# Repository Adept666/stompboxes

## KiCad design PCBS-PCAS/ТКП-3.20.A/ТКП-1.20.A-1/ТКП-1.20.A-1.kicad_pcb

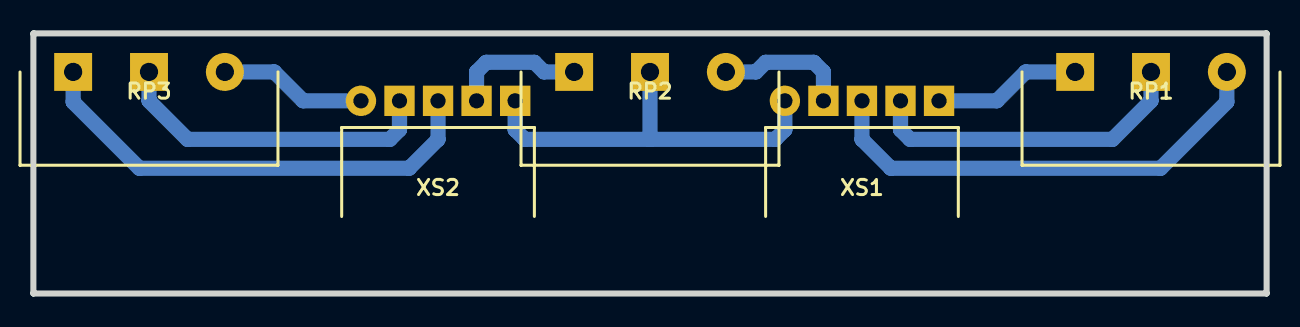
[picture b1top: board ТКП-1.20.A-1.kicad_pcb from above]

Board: 2 copper layers, 81.3 x 17.1 mm, 5 parts (0 on the bottom side), 9 nets.

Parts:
RP1: RP1: B100K; RP-PDB181-K-20-P
RP2: RP2: B5K; RP-PDB181-K-20-P
RP3: RP3: A500K; RP-PDB181-K-20-P
XS1, XS2: PBS-05R; CON-PBS-05R

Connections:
unnamed: RP1.1, XS1.3
unnamed: RP1.2, XS1.4
unnamed: RP1.3, XS1.5
unnamed: RP2.1, XS1.2
unnamed: RP2.2, XS1.1, XS2.5
unnamed: RP2.3, XS2.4
unnamed: RP3.1, XS2.1
unnamed: RP3.2, XS2.2
unnamed: RP3.3, XS2.3

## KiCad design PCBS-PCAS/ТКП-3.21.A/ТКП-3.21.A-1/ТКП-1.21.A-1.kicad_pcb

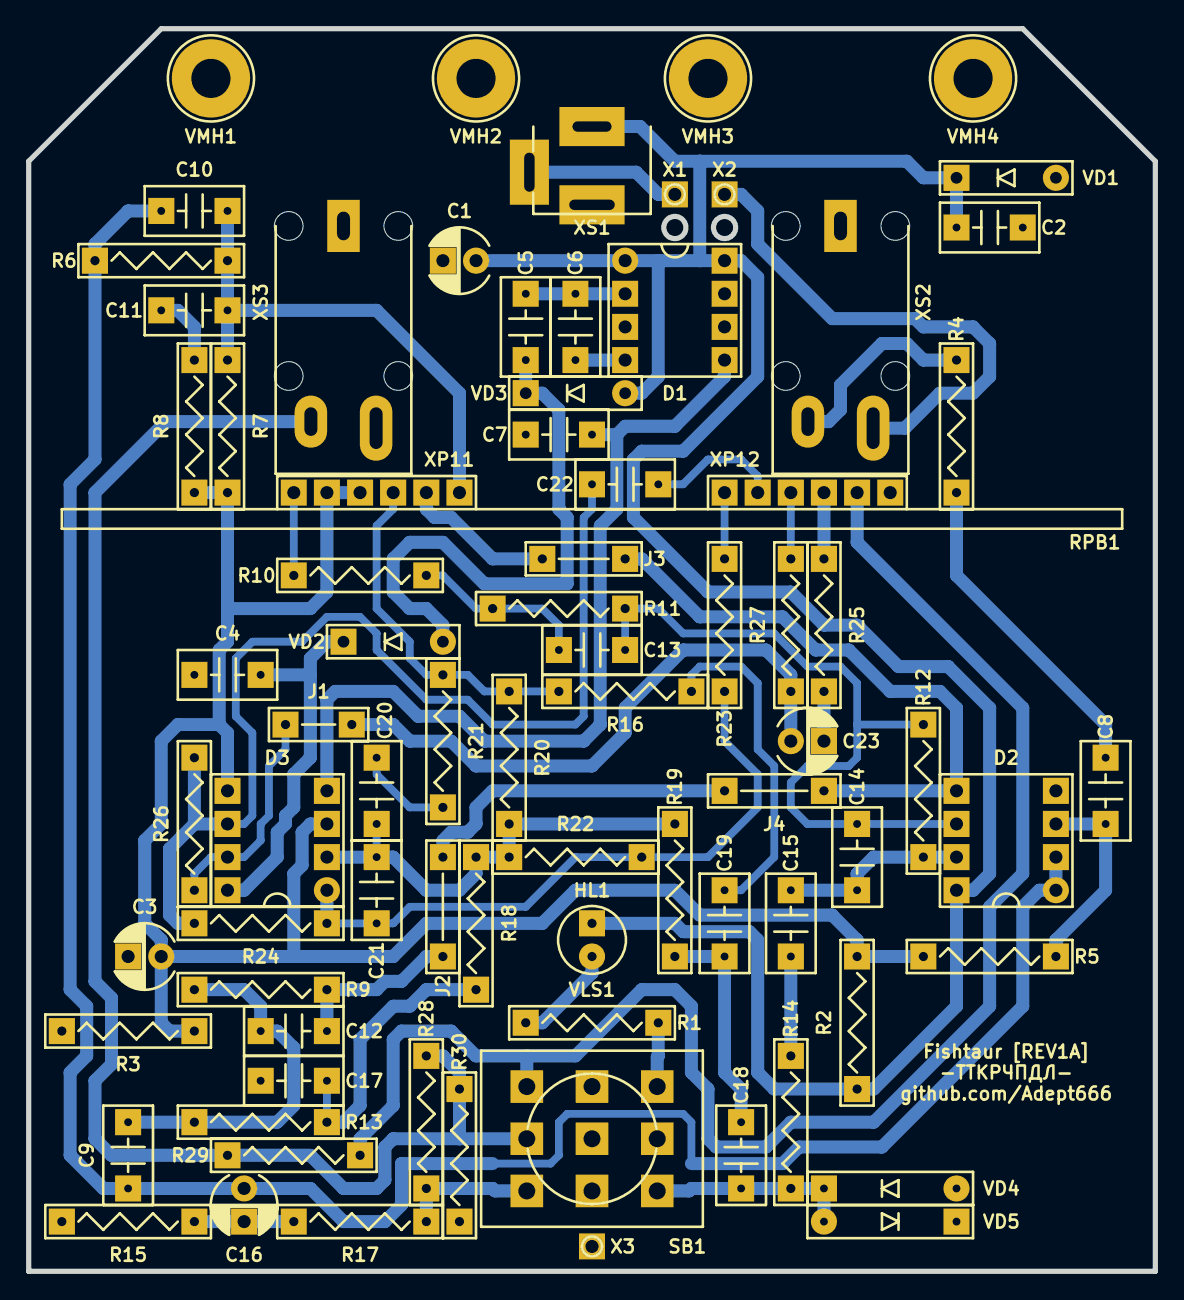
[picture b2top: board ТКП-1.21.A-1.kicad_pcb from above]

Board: 2 copper layers, 86.4 x 95.3 mm, 81 parts (0 on the bottom side), 44 nets.

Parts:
C1, C3: 476; CP-RADIAL-D05.0-P02.0-CLS
C2, C8, C9: 104; C-DISK-D04.2-T03.0-P05.08-d0.5
C4, C5, C6, C7, C15, C17, C18: 105; C-DISK-D04.2-T03.0-P05.08-d0.5
C10, C12: 683; C-DISK-D04.2-T03.0-P05.08-d0.5
C11: 334; C-DISK-D04.2-T03.0-P05.08-d0.5
C13: 823; C-DISK-D04.2-T03.0-P05.08-d0.5
C14: 391; C-DISK-D04.2-T03.0-P05.08-d0.5
C16, C23: 475; CP-RADIAL-D05.0-P02.0-CLS
C19: 222; C-DISK-D04.2-T03.0-P05.08-d0.5
C20: 223; C-DISK-D04.2-T03.0-P05.08-d0.5
C21: 821; C-DISK-D04.2-T03.0-P05.08-d0.5
C22: 392; C-DISK-D04.2-T03.0-P05.08-d0.5
D1: 7660S; P-DIP-08
D2, D3: 072; P-DIP-08
GB1: PP3; B-PP3-HV
HL1: FYL-5013UWC; LED-ROUND-05.0-UNI-SH-SPACER-PNL-5.3
J1: 0.6; J-TH-d0.6-P05.08
J2, J4: 0.6; J-TH-d0.6-P07.62
J3: 0.6; J-TH-d0.6-P06.35
R1, R4, R9: 103; R-MFR-25
R2, R3, R20: 273; R-MFR-25
R5: 105; R-MFR-25
R6: 512; R-MFR-25
R7, R13: 152; R-MFR-25
R8, R14: 102; R-MFR-25
R10: 202; R-MFR-25
R11, R18: 153; R-MFR-25
R12: 434; R-MFR-25
R15, R24, R26, R30: 104; R-MFR-25
R16: 223; R-MFR-25
R17, R25: 561; R-MFR-25
R19: 473; R-MFR-25
R21: 123; R-MFR-25
R22: 394; R-MFR-25
R23: 182; R-MFR-25
R27: 472; R-MFR-25
R28, R29: 683; R-MFR-25
RPB1: B100K-B10K-B10K; RPB-1590BB-18-3x17-DUAL-SINGLE-SINGLE-1.5-PNL-7.4-2.8
SB1: PBS-24-302SP; SW-PBS-24-302SP-2.5-PNL-13.0
VD1: 4742A; P-DO-41
VD2, VD3: 400x; P-DO-41
VD4, VD5: 34A; P-DO-7
VE1: 1590BB; 1590BB_B1
VLS1: BR-12.7; VLS-BR
VMH1, VMH2, VMH3, VMH4: DI5M3x18; VMH-STA-DA5-PNL-3.0
X1: +; CON-PAD-S-1.0-2.0
X2: -; CON-PAD-S-1.0-2.0
X3: COM; CON-PAD-S-1.0-2.0
XS1: DC-005; CON-DC-005
XS2: ST-008S-04; CON-ST-008X-04-OR-ST-008X-05
XS3: ST-008S-05; CON-ST-008X-04-OR-ST-008X-05

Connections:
/BYPASS: R17.2, R28.1, SB1.NC1
/EFFECT: R29.1, RPB1.32, SB1.NO1
/IN: R4.1, XS2.T
/J1: C23.+, D3.7, J1.J, R26.2, R27.2
/J2: C12.2, D2.5, J2.J, J3.J, J4.J, R9.2, RPB1.11
/LED: R1.1, SB1.NO3
/LED-CIR: C18.1, R14.2, SB1.NC3, VD4.C, VD5.A
/OUT: R28.2, R29.2, R30.2, SB1.COM1, XS3.T
/PP3-NEG: X2.1, XS2.R/TN
/PP3-POS: X1.1, XS1.SN
COM: C1.-, C2.2, C3.-, C4.2, C7.1, C17.2, D1.3, D2.4, R3.1, R15.1, R30.1, RPB1.31, SB1.COM2, SB1.COM3, SB1.NC2, VD1.A, VD4.A, VD5.C, VMH1.0, VMH2.0, VMH3.0, VMH4.0, X3.1, XS1.C, XS2.S, XS3.S
unnamed: C5.1, VD2.A, VD3.C
unnamed: C5.2, C6.1, D1.2
unnamed: C6.2, D1.4
unnamed: C8.1, R4.2
unnamed: C8.2, D2.3, R5.2
unnamed: C9.1, C10.1, C16.+, D2.1, D2.2, R6.2
unnamed: C10.2, C11.1, R6.1, R7.2, RPB1.14
unnamed: C11.2, R8.2
unnamed: C9.2, C12.1, R9.1, R13.1
unnamed: C13.1, R10.1, R11.1
unnamed: C13.2, C14.1, D2.6, R11.2, R12.1
unnamed: C14.2, C15.1, D2.7, R12.2
unnamed: C15.2, R14.1
unnamed: C16.-, R15.2, R17.1
unnamed: C17.1, R13.2, R18.1
unnamed: C18.2, C19.1, R19.1
unnamed: C19.2, R16.2
unnamed: C20.1, C21.1, D3.2, R18.2, R19.2, R20.2, R22.1
unnamed: C20.2, R21.2
unnamed: C21.2, D3.1, R22.2, R23.1, R24.1
unnamed: C22.1, RPB1.22
unnamed: C22.2, D3.6, R24.2, R26.1
unnamed: C23.-, R25.1
unnamed: HL1.C, R1.2
unnamed: R10.2, RPB1.13
unnamed: R16.1, R20.1, R21.1, RPB1.15
unnamed: R23.2, RPB1.23
unnamed: R25.2, RPB1.33
unnamed: R27.1, RPB1.21
VA: C1.+, C2.1, D1.1, D1.8, D2.8, HL1.A, R2.2, VD1.C, VD3.A, XS1.S
VB: C4.1, D3.8, VD2.C
VC: C7.2, D1.5, D3.4
VREF: C3.+, D3.3, D3.5, R2.1, R3.2, R5.1, R7.1, R8.1, RPB1.12, RPB1.16

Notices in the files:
PCBS-PCAS/ТКП-3.20.A/ТКП-1.20.A-1/ТКП-1.20.A-1.kicad_pcb:
This project is licensed under GNU General Public License v3.0 or later
